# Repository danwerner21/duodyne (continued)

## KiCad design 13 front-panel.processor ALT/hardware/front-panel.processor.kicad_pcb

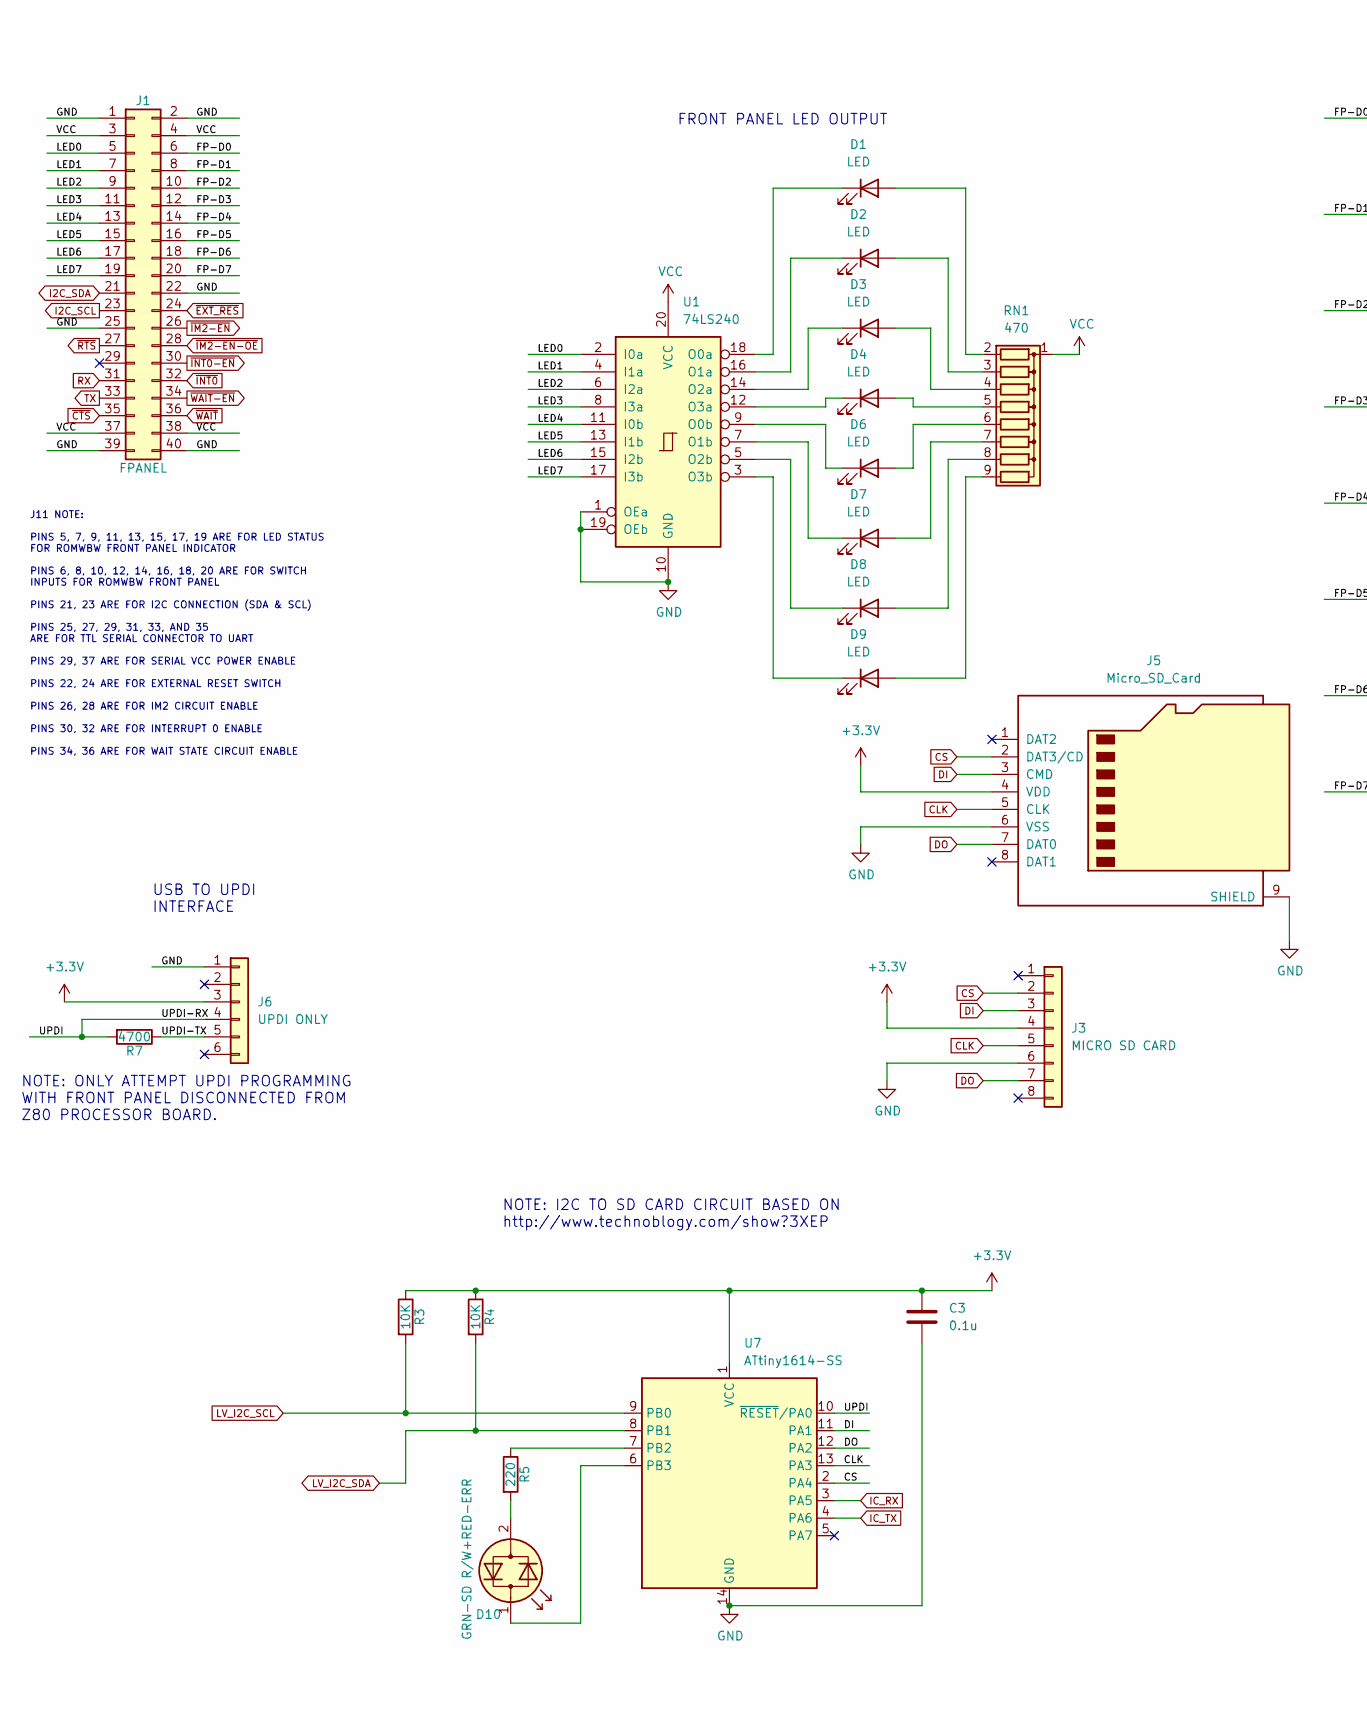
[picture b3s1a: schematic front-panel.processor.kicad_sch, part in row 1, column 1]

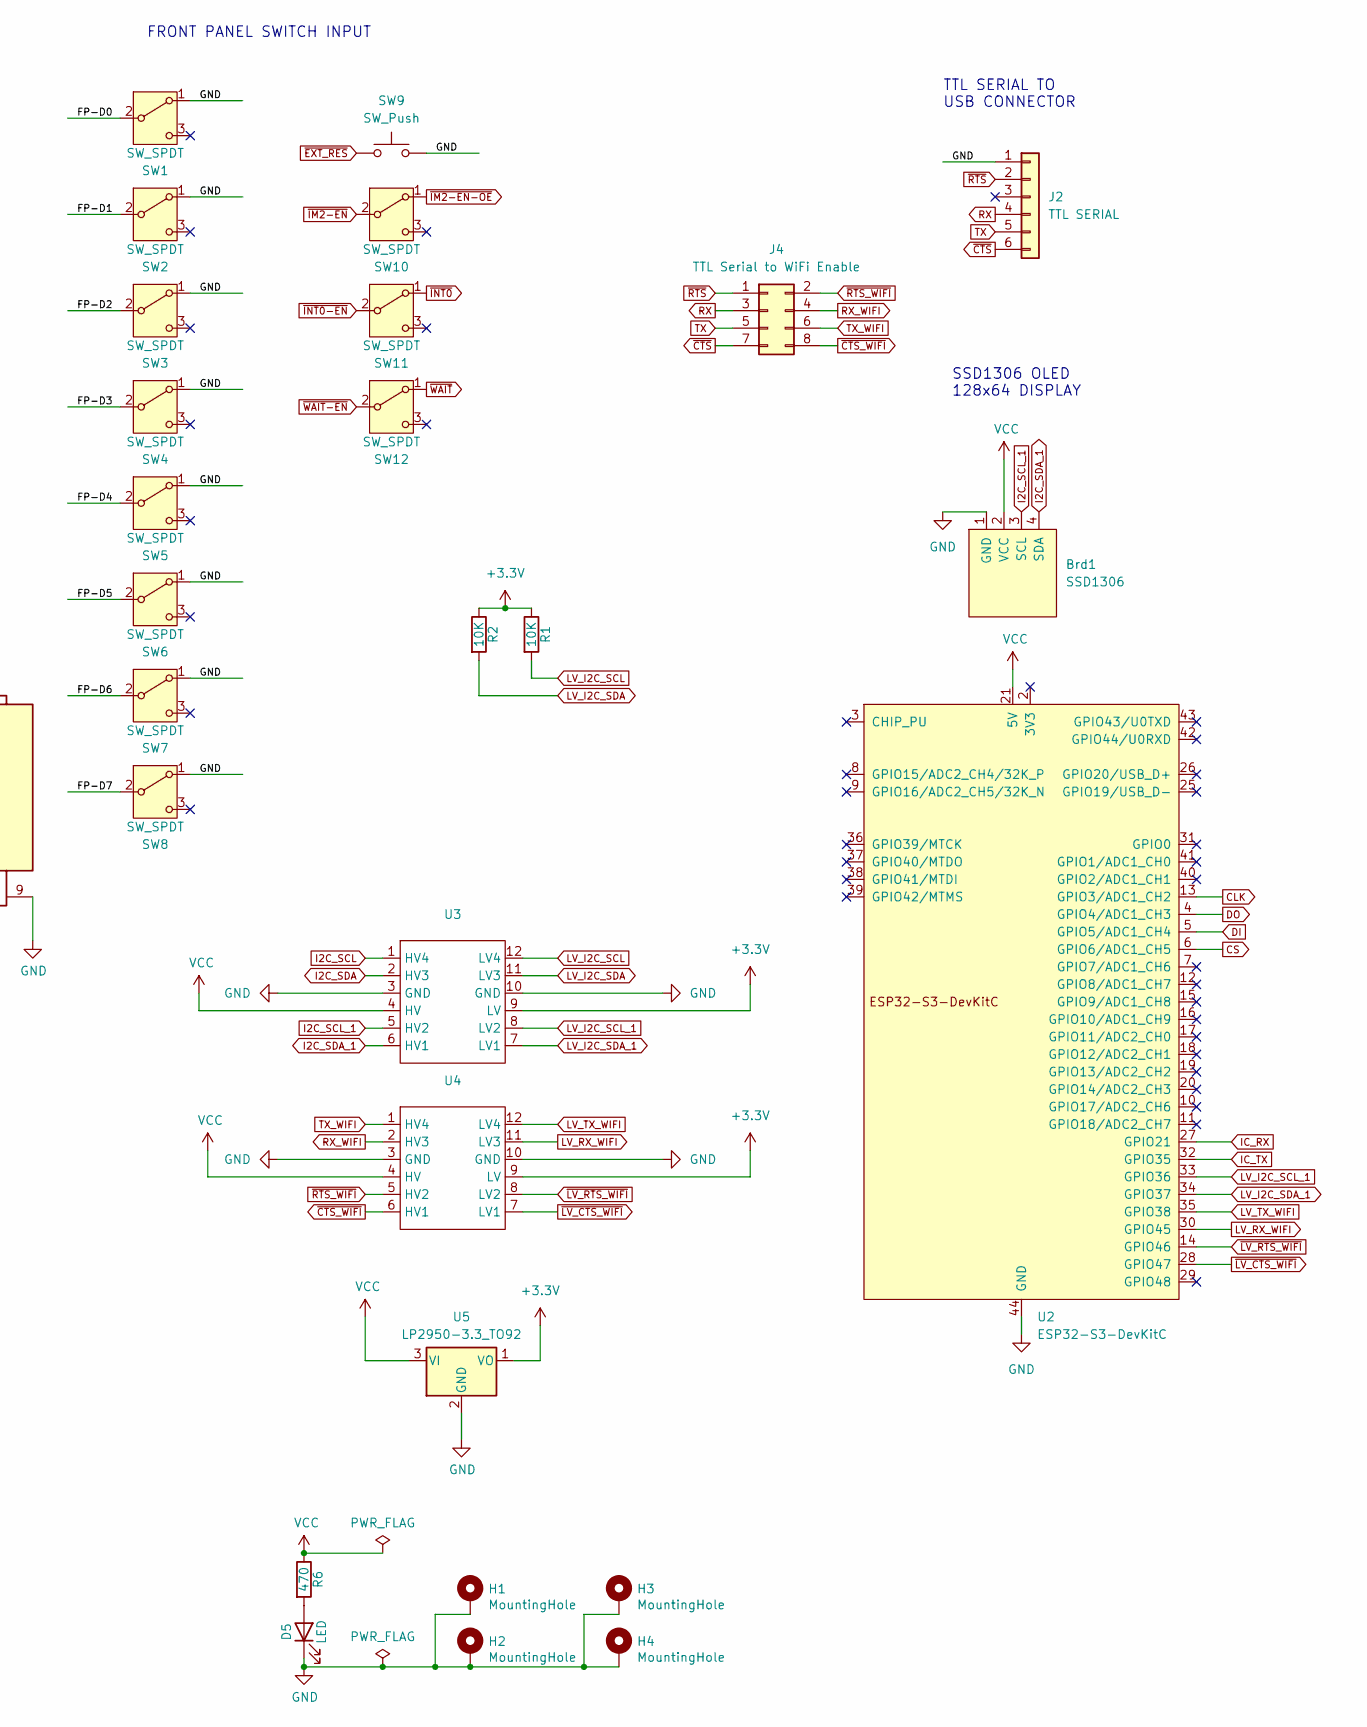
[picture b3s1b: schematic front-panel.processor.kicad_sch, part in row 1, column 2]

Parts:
Brd1: SSD1306; 128x64OLED
C3: 0.1u; C_Disc_D5.0mm_W2.5mm_P5.00mm
D1, D2, D3, D4, D5, D6, D7, D8, D9: LED; LED_D3.0mm
D10: GRN-SD R/W+RED-ERR; LED_D5.0mm
H1, H2, H3, H4: MountingHole; MountingHole_3.2mm_M3_Pad
J1: FPANEL; IDC-Header_2x20_P2.54mm_Horizontal
J2: TTL SERIAL; PinHeader_1x06_P2.54mm_Vertical
J3: MICRO SD CARD; PinSocket_1x08_P2.54mm_Vertical
J4: TTL Serial to WiFi Enable; PinHeader_2x04_P2.54mm_Vertical
J5: Micro_SD_Card; SD_Hirose_DM1AA_SF_PEJ82
J6: UPDI ONLY; PinHeader_1x06_P2.54mm_Vertical
R1, R2, R3, R4: 10K; R_Axial_DIN0207_L6.3mm_D2.5mm_P7.62mm_Horizontal
R5: 220; R_Axial_DIN0207_L6.3mm_D2.5mm_P7.62mm_Horizontal
R6: 470; R_Axial_DIN0207_L6.3mm_D2.5mm_P7.62mm_Horizontal
R7: 4700; R_Axial_DIN0207_L6.3mm_D2.5mm_P7.62mm_Horizontal
RN1: 470; R_Array_SIP9
SW1, SW2, SW3, SW4, SW5, SW6, SW7, SW8, SW10, SW11, SW12: SW_SPDT; SW_Toggle_Blue_wSlots
SW9: SW_Push; SW_PUSH_6mm
U1: 74LS240; DIP-20_W7.62mm
U2: ESP32-S3-DevKitC; ESP32S3Devkit3Universal
U3, U4: HV-LV
U5: LP2950-3.3_TO92; TO-92_Inline
U7: ATtiny1614-SS; SOIC-14_3.9x8.7mm_P1.27mm

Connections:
+3.3V: C3.2, J3.4, J5.4 (VDD), J6.3, R1.1, R2.1, R3.1, R4.1, U3.9 (LV), U4.9 (LV), U5.1 (VO), U7.1 (VCC)
/FP-D0: J1.6, SW1.2 (B)
/FP-D1: J1.8, SW2.2 (B)
/FP-D2: J1.10, SW3.2 (B)
/FP-D3: J1.12, SW4.2 (B)
/FP-D4: J1.14, SW5.2 (B)
/FP-D5: J1.16, SW6.2 (B)
/FP-D6: J1.18, SW7.2 (B)
/FP-D7: J1.20, SW8.2 (B)
/LED0: J1.5, U1.2 (I0a)
/LED1: J1.7, U1.4 (I1a)
/LED2: J1.9, U1.6 (I2a)
/LED3: J1.11, U1.8 (I3a)
/LED4: J1.13, U1.11 (I0b)
/LED5: J1.15, U1.13 (I1b)
/LED6: J1.17, U1.15 (I2b)
/LED7: J1.19, U1.17 (I3b)
/UPDI: J6.4, R7.2, U7.10 (~RESET/PA0)
/UPDI-TX: J6.5, R7.1
CLK: J3.5, J5.5 (CLK), U2.13 (GPIO3/ADC1_CH2), U7.13 (PA3)
CS: J3.2, J5.2 (DAT3/CD), U2.6 (GPIO6/ADC1_CH5), U7.2 (PA4)
DI: J3.3, J5.3 (CMD), U2.5 (GPIO5/ADC1_CH4), U7.11 (PA1)
DO: J3.7, J5.7 (DAT0), U2.4 (GPIO4/ADC1_CH3), U7.12 (PA2)
GND: Brd1.1 (GND), C3.1, D5.1 (K), H1.1, H2.1, H3.1, H4.1, J1.1, J1.2, J1.22, J1.25, J1.39, J1.40, J2.1, J3.6, J5.6 (VSS), J5.9 (SHIELD), J6.1, SW1.1 (A), SW2.1 (A), SW3.1 (A), SW4.1 (A), SW5.1 (A), SW6.1 (A), SW7.1 (A), SW8.1 (A), SW9.2, U1.1 (OEa), U1.10 (GND), U1.19 (OEb), U2.22 (GND), U2.23 (GND), U2.24 (GND), U2.44 (GND), U3.3 (GND), U3.10 (GND), U4.3 (GND), U4.10 (GND), U5.2 (GND), U7.14 (GND)
I2C_SCL: J1.23, U3.1 (HV4)
I2C_SCL_1: Brd1.3 (SCL), U3.5 (HV2)
I2C_SDA: J1.21, U3.2 (HV3)
I2C_SDA_1: Brd1.4 (SDA), U3.6 (HV1)
IC_RX: U2.27 (GPIO21), U7.3 (PA5)
IC_TX: U2.32 (GPIO35), U7.4 (PA6)
LV_I2C_SCL: R1.2, R3.2, U3.12 (LV4), U7.9 (PB0)
LV_I2C_SCL_1: U2.33 (GPIO36), U3.8 (LV2)
LV_I2C_SDA: R2.2, R4.2, U3.11 (LV3), U7.8 (PB1)
LV_I2C_SDA_1: U2.34 (GPIO37), U3.7 (LV1)
LV_RX_WIFI: U2.30 (GPIO45), U4.11 (LV3)
LV_TX_WIFI: U2.35 (GPIO38), U4.12 (LV4)
unnamed: D1.2 (A), RN1.2 (R1)
unnamed: D1.1 (K), U1.18 (O0a)
unnamed: D2.2 (A), RN1.3 (R2)
unnamed: D2.1 (K), U1.16 (O1a)
unnamed: D3.2 (A), RN1.4 (R3)
unnamed: D3.1 (K), U1.14 (O2a)
unnamed: D4.2 (A), RN1.5 (R4)
unnamed: D4.1 (K), U1.12 (O3a)
unnamed: D5.2 (A), R6.2
unnamed: D6.2 (A), RN1.6 (R5)
unnamed: D6.1 (K), U1.9 (O0b)
unnamed: D7.2 (A), RN1.7 (R6)
unnamed: D7.1 (K), U1.7 (O1b)
unnamed: D8.2 (A), RN1.8 (R7)
unnamed: D8.1 (K), U1.5 (O2b)
unnamed: D9.2 (A), RN1.9 (R8)
unnamed: D9.1 (K), U1.3 (O3b)
unnamed: D10.2 (AK), R5.2
unnamed: D10.1 (KA), U7.6 (PB3)
unnamed: R5.1, U7.7 (PB2)
RX: J1.31, J2.4, J4.3
RX_WIFI: J4.4, U4.2 (HV3)
TX: J1.33, J2.5, J4.5
TX_WIFI: J4.6, U4.1 (HV4)
VCC: Brd1.2 (VCC), J1.3, J1.4, J1.37, J1.38, R6.1, RN1.1 (common), U1.20 (VCC), U2.21 (5V), U3.4 (HV), U4.4 (HV), U5.3 (VI)
~CTS_WIFI: J4.8, U4.6 (HV1)
~CTS: J1.35, J2.6, J4.7
~EXT_RES: J1.24, SW9.1
~IM2-EN-OE: J1.28, SW10.1 (A)
~IM2-EN: J1.26, SW10.2 (B)
~INT0-EN: J1.30, SW11.2 (B)
~INT0: J1.32, SW11.1 (A)
~LV_CTS_WIFI: U2.28 (GPIO47), U4.7 (LV1)
~LV_RTS_WIFI: U2.14 (GPIO46), U4.8 (LV2)
~RTS_WIFI: J4.2, U4.5 (HV2)
~RTS: J1.27, J2.2, J4.1
~WAIT-EN: J1.34, SW12.2 (B)
~WAIT: J1.36, SW12.1 (A)

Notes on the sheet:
SSD1306 OLED 128x64 DISPLAY
FRONT PANEL LED OUTPUT
USB TO UPDI INTERFACE
J11 NOTE: PINS 5, 7, 9, 11, 13, 15, 17, 19 ARE FOR LED STATUS FOR ROMWBW FRONT PANEL INDICATOR PINS 6, 8, 10, 12, 14, 16, 18, 20 ARE FOR SWITCH INPUTS FOR ROMWBW FRONT PANEL PINS 21, 23 ARE FOR I2C CONNECTION (SDA & SCL) PINS 25, 27, 29, 31, 33, AND 35 ARE FOR TTL SERIAL CONNECTOR TO UART PINS 29, 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
NOTE: I2C TO SD CARD CIRCUIT BASED ON http://www.technoblogy.com/show?3XEP
NOTE: ONLY ATTEMPT UPDI PROGRAMMING WITH FRONT PANEL DISCONNECTED FROM Z80 PROCESSOR BOARD.
FRONT PANEL SWITCH INPUT
TTL SERIAL TO USB CONNECTOR

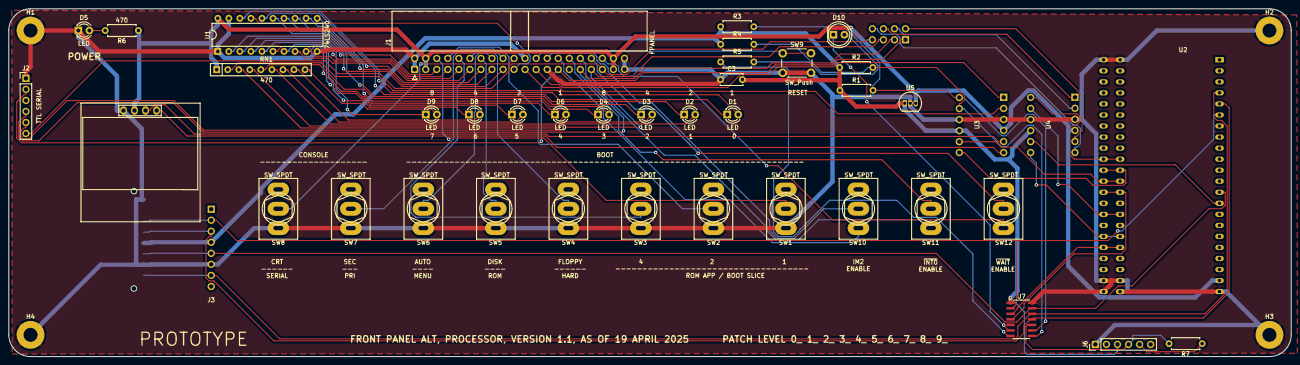
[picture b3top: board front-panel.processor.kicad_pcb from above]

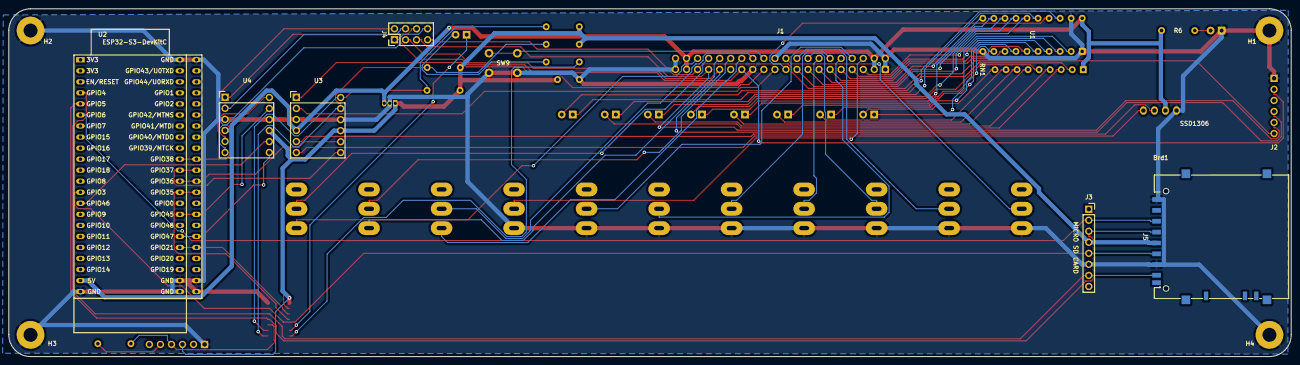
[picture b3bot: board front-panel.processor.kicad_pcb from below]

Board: 2 copper layers, 295.0 x 80.0 mm, 48 parts (6 on the bottom side), 74 nets.

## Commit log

2025-04-13 02 and 265
2025-05-05 duodyne 6502 work
